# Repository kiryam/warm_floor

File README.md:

# Absolutely no warranty USE ON YOUR OWN RISK

# About this project
This project I started when I finished my home lab in balcony of my house.
I found that it is very cold in december. I decided to install floor heater to make temperature comfortable,
but first attempt been wrong. I had very hot floor. I decided to make floor heater with 5 zones (unformattly right now device have support for 6 zones)

# Hardware
## High voltage module
todo

## Logic module
todo

## Controller module
todo

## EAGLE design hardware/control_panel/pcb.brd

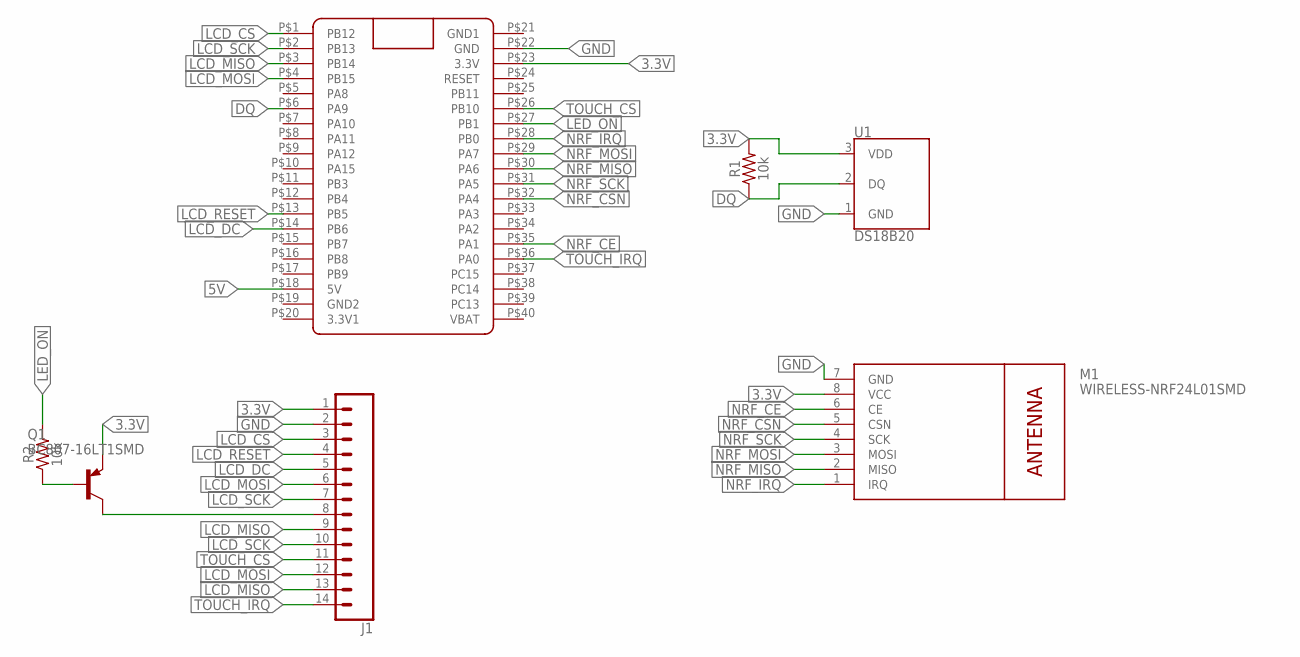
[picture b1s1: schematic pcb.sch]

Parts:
J1: CONN_14; 1X14
M1: WIRELESS-NRF24L01SMD; WIRELESS-NRF24L01-SMD
Q1: BC807-16LT1SMD; SOT23-BEC
R1, R2: 10k; 0603
U1: DS18B20; TO-92-AMMO
U$1: BLUE_PILL

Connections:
3.3V: J1.1, M1.8 (VCC), Q1.E, R1.2, U1.3 (VDD), U$1.P$23 (3.3V)
5V: U$1.P$18 (5V)
DQ: R1.1, U1.2 (DQ), U$1.P$6 (PA9)
GND: J1.2, M1.7 (GND), U1.1 (GND), U$1.P$22 (GND)
GND1: U$1.P$21 (GND1)
LCD_CS: J1.3, U$1.P$1 (PB12)
LCD_DC: J1.5, U$1.P$14 (PB6)
LCD_MISO: J1.9, J1.13, U$1.P$3 (PB14)
LCD_MOSI: J1.6, J1.12, U$1.P$4 (PB15)
LCD_RESET: J1.4, U$1.P$13 (PB5)
LCD_SCK: J1.7, J1.10, U$1.P$2 (PB13)
LED_ON: R2.2, U$1.P$27 (PB1)
unnamed: Q1.B, R2.1
unnamed: J1.8, Q1.C
NRF_CE: M1.6 (CE), U$1.P$35 (PA1)
NRF_CSN: M1.5 (CSN), U$1.P$32 (PA4)
NRF_IRQ: M1.1 (IRQ), U$1.P$28 (PB0)
NRF_MISO: M1.2 (MISO), U$1.P$30 (PA6)
NRF_MOSI: M1.3 (MOSI), U$1.P$29 (PA7)
NRF_SCK: M1.4 (SCK), U$1.P$31 (PA5)
TOUCH_CS: J1.11, U$1.P$26 (PB10)
TOUCH_IRQ: J1.14, U$1.P$36 (PA0)

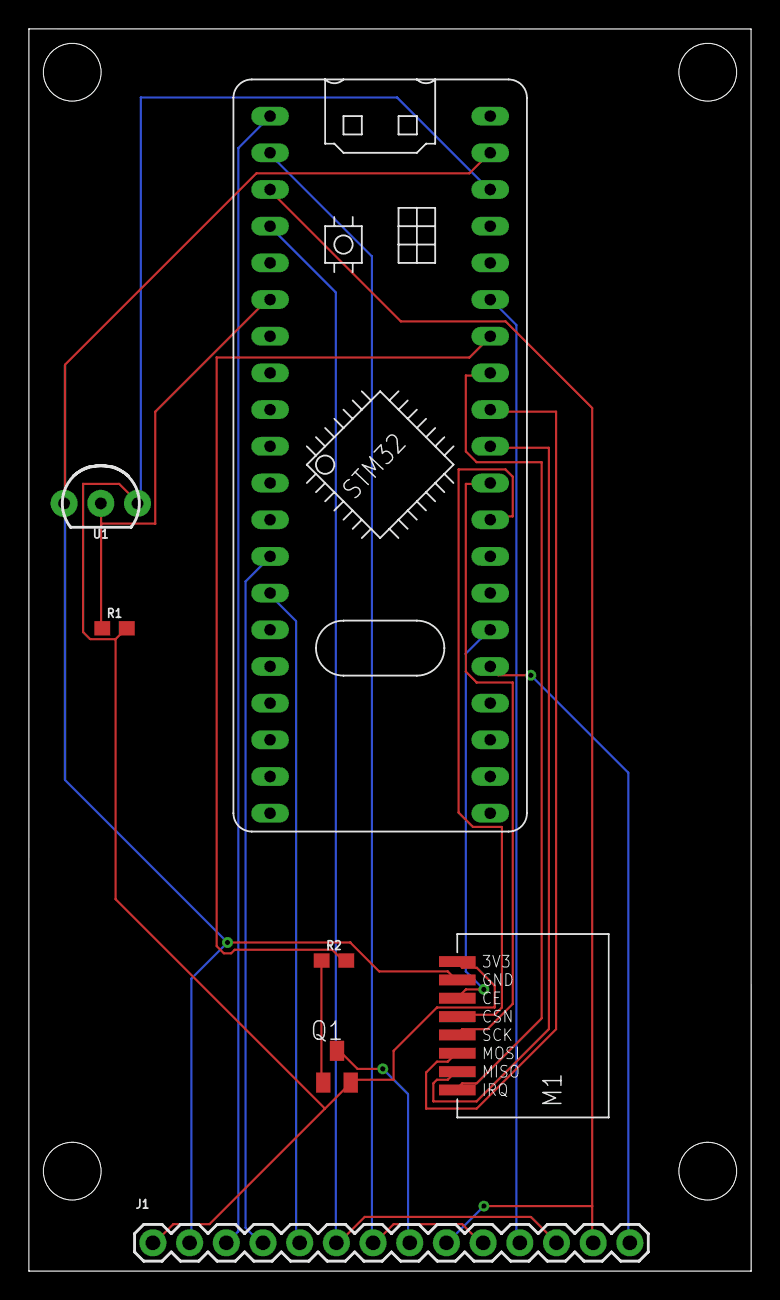
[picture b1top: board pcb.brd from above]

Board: 2 copper layers, 50.0 x 86.0 mm, 7 parts (0 on the bottom side), 20 nets.

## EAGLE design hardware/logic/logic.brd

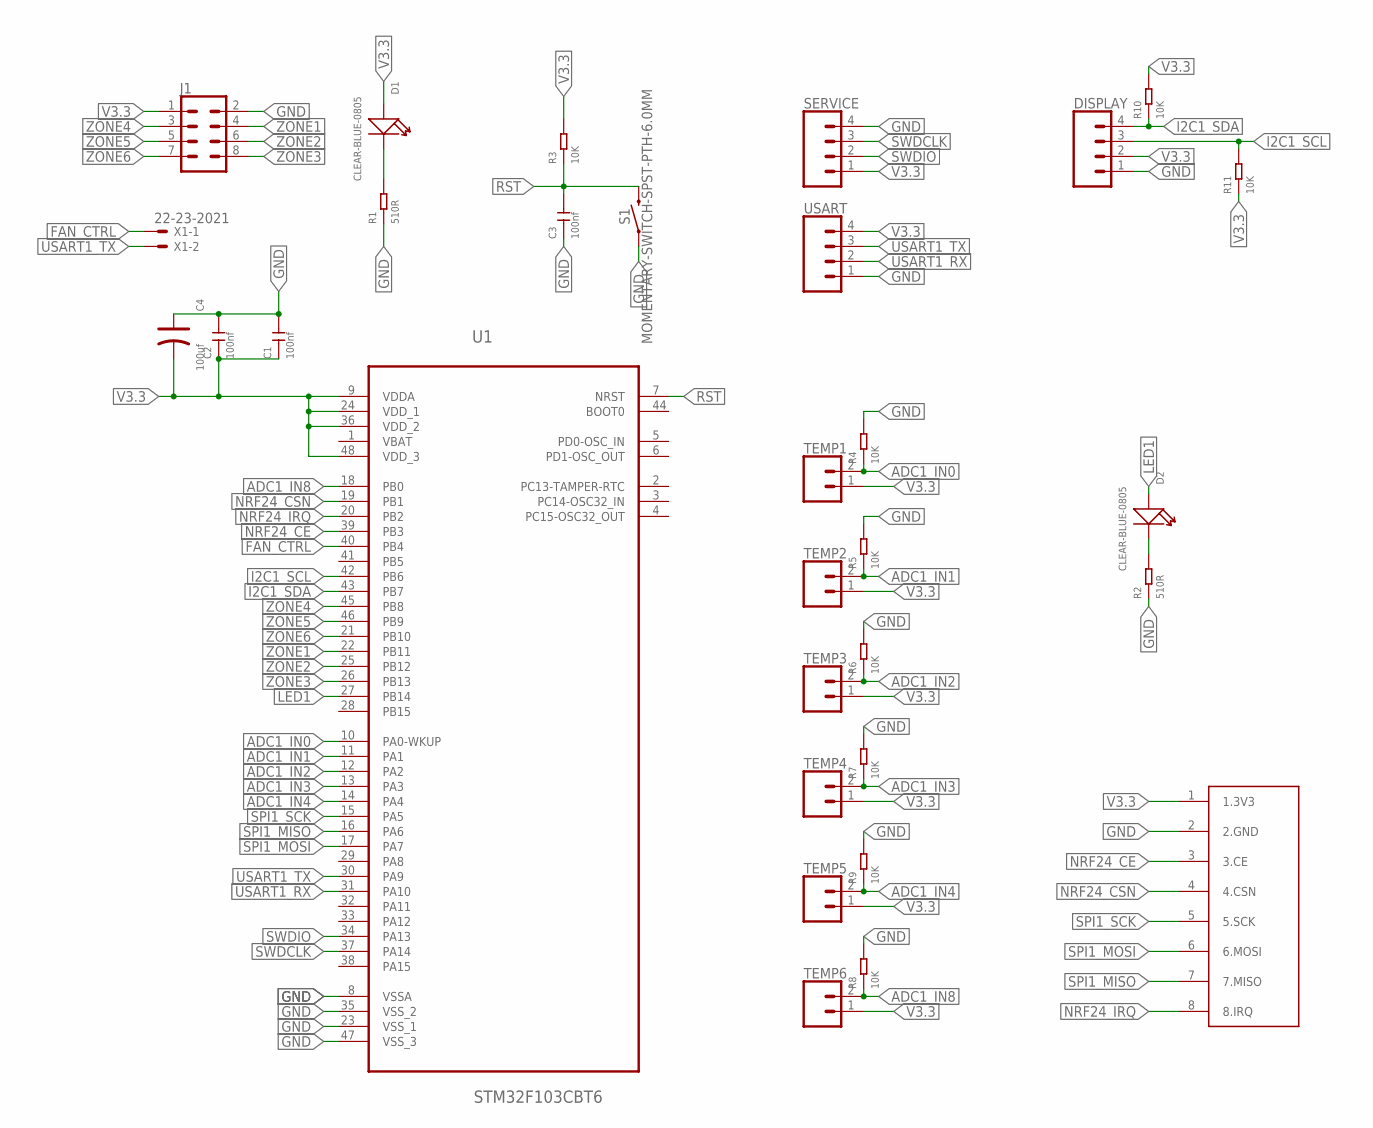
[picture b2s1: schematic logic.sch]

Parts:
C1, C2, C3: 100nf; C0805
C4: 100uf; AVX-B
D1, D2: CLEAR-BLUE-0805; LED-0805
DISPLAY: CONN_04; 1X04
J1: CONN_04X2; 2X4
R1, R2: 510R; R0603
R3, R4, R5, R6, R7, R8, R9, R10, R11: 10K; R0805
S1: MOMENTARY-SWITCH-SPST-PTH-6.0MM; TACTILE_SWITCH_PTH_6.0MM
SERVICE: CONN_04; 1X04
TEMP1, TEMP2, TEMP3, TEMP4, TEMP5, TEMP6: CONN_02; 1X02
U1: STM32F103CBT6; QFP50P900X900X160-48N
U$2: NRF24L01+
USART: CONN_04; 1X04
X1: 22-23-2021

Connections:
ADC1_IN0: R4.1, TEMP1.2, U1.10 (PA0-WKUP)
ADC1_IN1: R5.1, TEMP2.2, U1.11 (PA1)
ADC1_IN2: R6.1, TEMP3.2, U1.12 (PA2)
ADC1_IN3: R7.1, TEMP4.2, U1.13 (PA3)
ADC1_IN4: R9.1, TEMP5.2, U1.14 (PA4)
ADC1_IN8: R8.1, TEMP6.2, U1.18 (PB0)
FAN_CTRL: U1.40 (PB4), X1.1
GND: C1.2, C2.2, C3.1, C4.+, DISPLAY.1, J1.2, R1.1, R2.1, R4.2, R5.2, R6.2, R7.2, R8.2, R9.2, S1.1, SERVICE.4, U1.8 (VSSA), U1.23 (VSS_1), U1.35 (VSS_2), U1.47 (VSS_3), U$2.2 (2.GND), USART.1
I2C1_SCL: DISPLAY.3, R11.2, U1.42 (PB6)
I2C1_SDA: DISPLAY.4, R10.1, U1.43 (PB7)
LED1: D2.+, U1.27 (PB14)
unnamed: D1.-, R1.2
unnamed: D2.-, R2.2
NRF24_CE: U1.39 (PB3), U$2.3 (3.CE)
NRF24_CSN: U1.19 (PB1), U$2.4 (4.CSN)
NRF24_IRQ: U1.20 (PB2), U$2.8 (8.IRQ)
PA11: U1.32 (PA11)
RST: C3.2, R3.1, S1.3 (2), U1.7 (NRST)
SPI1_MISO: U1.16 (PA6), U$2.7 (7.MISO)
SPI1_MOSI: U1.17 (PA7), U$2.6 (6.MOSI)
SPI1_SCK: U1.15 (PA5), U$2.5 (5.SCK)
SWDCLK: SERVICE.3, U1.37 (PA14)
SWDIO: SERVICE.2, U1.34 (PA13)
USART1_RX: U1.31 (PA10), USART.2
USART1_TX: U1.30 (PA9), USART.3, X1.2
V3.3: C1.1, C2.1, C4.-, D1.+, DISPLAY.2, J1.1, R3.2, R10.2, R11.1, SERVICE.1, TEMP1.1, TEMP2.1, TEMP3.1, TEMP4.1, TEMP5.1, TEMP6.1, U1.9 (VDDA), U1.24 (VDD_1), U1.36 (VDD_2), U1.48 (VDD_3), U$2.1 (1.3V3), USART.4
ZONE1: J1.4, U1.22 (PB11)
ZONE2: J1.6, U1.25 (PB12)
ZONE3: J1.8, U1.26 (PB13)
ZONE4: J1.3, U1.45 (PB8)
ZONE5: J1.5, U1.46 (PB9)
ZONE6: J1.7, U1.21 (PB10)

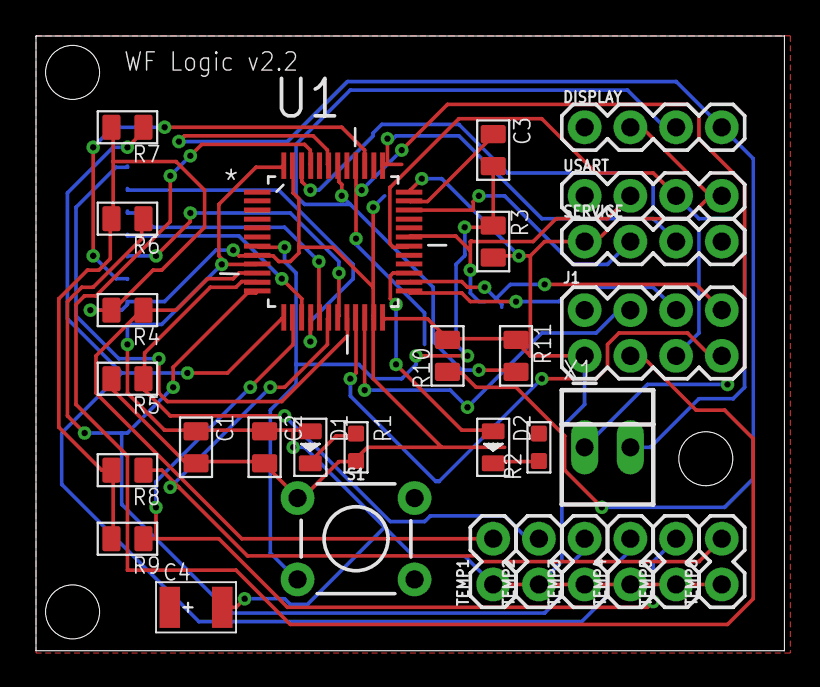
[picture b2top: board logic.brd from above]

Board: 2 copper layers, 41.6 x 34.2 mm, 31 parts (1 on the bottom side), 31 nets.

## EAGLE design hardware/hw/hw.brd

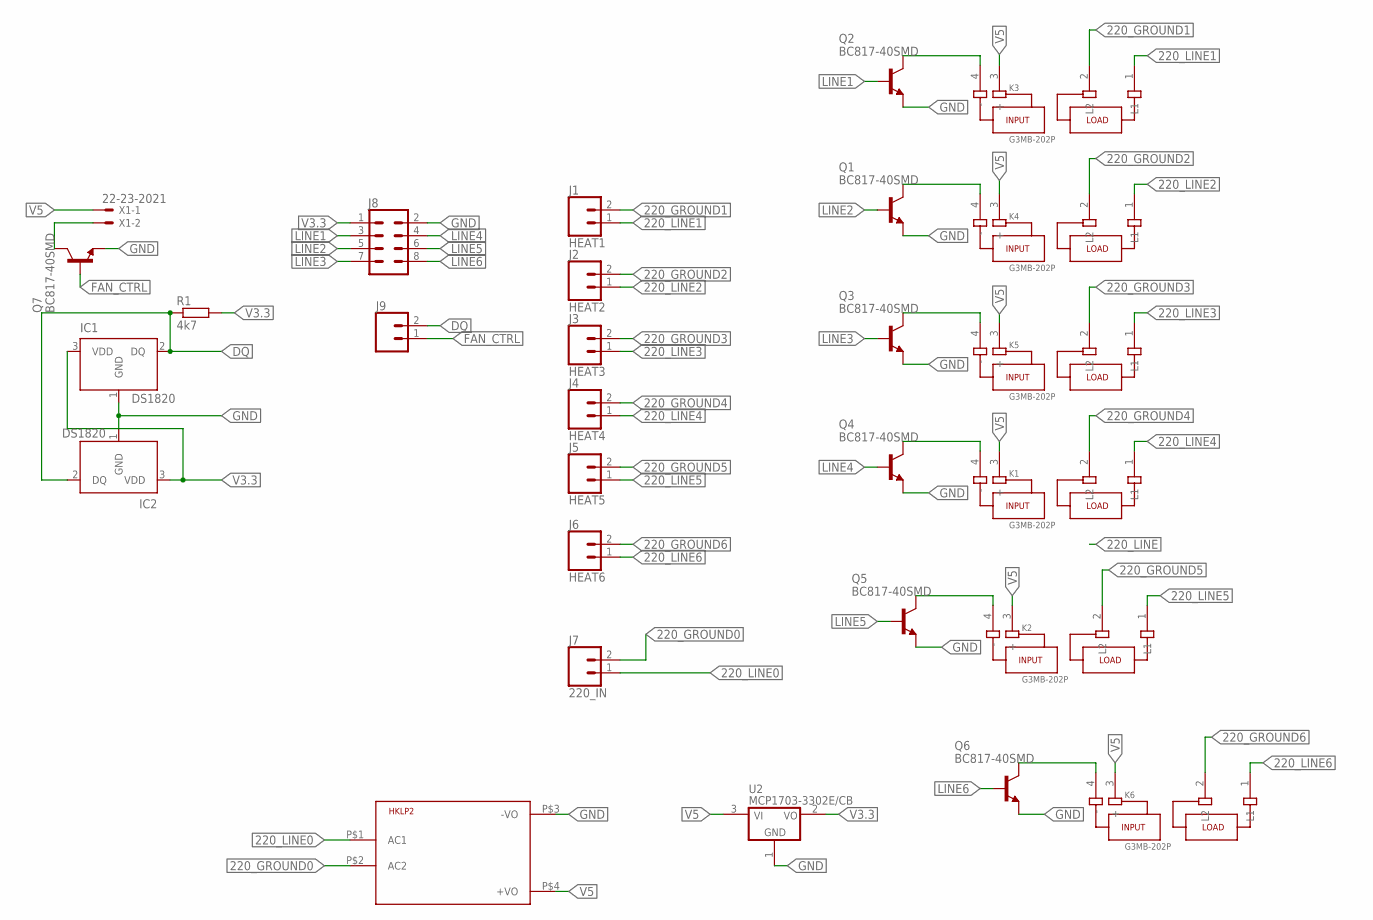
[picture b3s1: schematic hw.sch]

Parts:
HKLP2: HKLPM01
IC1, IC2: DS1820; TO-92
J1: HEAT1; SCREWTERMINAL-5MM-2
J2: HEAT2; SCREWTERMINAL-5MM-2
J3: HEAT3; SCREWTERMINAL-5MM-2
J4: HEAT4; SCREWTERMINAL-5MM-2
J5: HEAT5; SCREWTERMINAL-5MM-2
J6: HEAT6; SCREWTERMINAL-5MM-2
J7: 220_IN; SCREWTERMINAL-5MM-2
J8: CONN_04X2; 2X4
J9: CONN_02; 1X02
K1, K2, K3, K4, K5, K6: G3MB-202P; RELAY_G3MB-202P
Q1, Q2, Q3, Q4, Q5, Q6, Q7: BC817-40SMD; SOT23-BEC
R1: 4k7; R0805
U2: MCP1703-3302E/CB; SOT23A_MICROCHIP_CB
X1: 22-23-2021

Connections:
220_GROUND0: HKLP2.P$2 (AC2), J7.2
220_GROUND1: J1.2, K3.2 (L2)
220_GROUND2: J2.2, K4.2 (L2)
220_GROUND3: J3.2, K5.2 (L2)
220_GROUND4: J4.2, K1.2 (L2)
220_GROUND5: J5.2, K2.2 (L2)
220_GROUND6: J6.2, K6.2 (L2)
220_LINE0: HKLP2.P$1 (AC1), J7.1
220_LINE1: J1.1, K3.1 (L1)
220_LINE2: J2.1, K4.1 (L1)
220_LINE3: J3.1, K5.1 (L1)
220_LINE4: J4.1, K1.1 (L1)
220_LINE5: J5.1, K2.1 (L1)
220_LINE6: J6.1, K6.1 (L1)
DQ: IC1.2 (DQ), IC2.2 (DQ), J9.2, R1.1
FAN_CTRL: J9.1, Q7.B
GND: HKLP2.P$3 (-VO), IC1.1 (GND), IC2.1 (GND), J8.2, Q1.E, Q2.E, Q3.E, Q4.E, Q5.E, Q6.E, Q7.E, U2.1 (GND)
LINE1: J8.3, Q2.B
LINE2: J8.5, Q1.B
LINE3: J8.7, Q3.B
LINE4: J8.4, Q4.B
LINE5: J8.6, Q5.B
LINE6: J8.8, Q6.B
unnamed: K2.4 (-), Q5.C
unnamed: K3.4 (-), Q2.C
unnamed: K6.4 (-), Q6.C
unnamed: K4.4 (-), Q1.C
unnamed: K5.4 (-), Q3.C
unnamed: K1.4 (-), Q4.C
unnamed: Q7.C, X1.2
V3.3: IC1.3 (VDD), IC2.3 (VDD), J8.1, R1.2, U2.2 (VO)
V5: HKLP2.P$4 (+VO), K1.3 (+), K2.3 (+), K3.3 (+), K4.3 (+), K5.3 (+), K6.3 (+), U2.3 (VI), X1.1

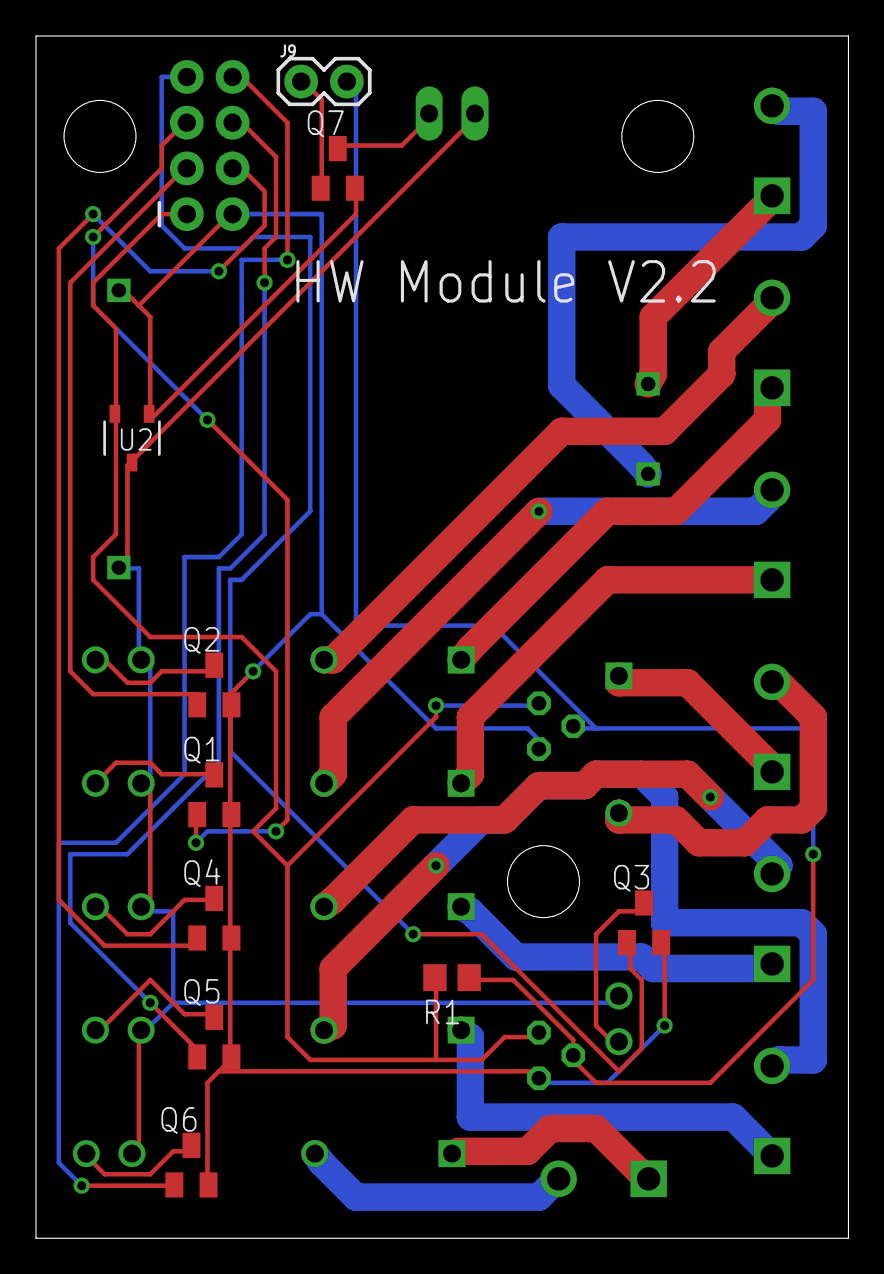
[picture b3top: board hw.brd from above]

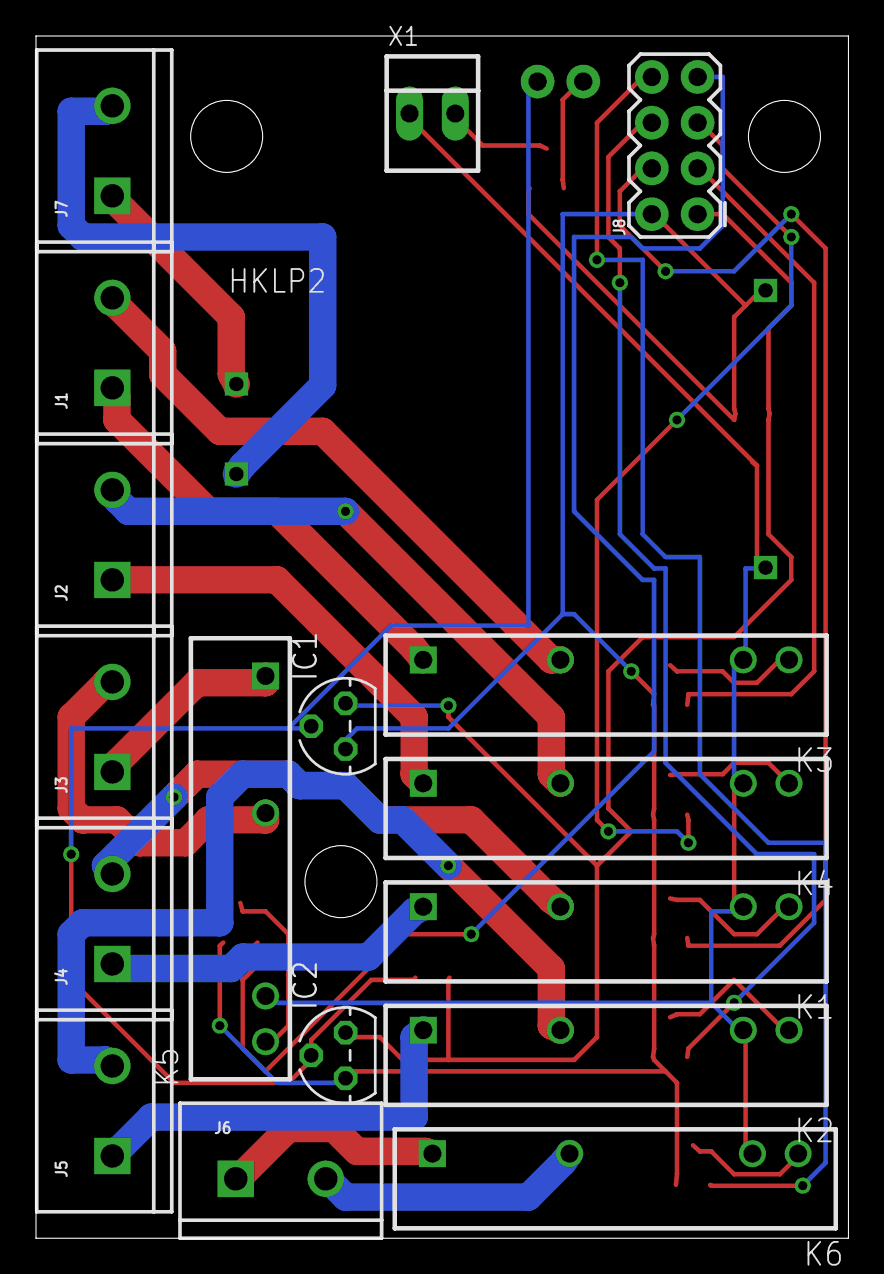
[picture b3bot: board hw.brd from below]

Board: 2 copper layers, 45.1 x 66.8 mm, 28 parts (18 on the bottom side), 32 nets.

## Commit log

2018-06-06 hardware
2018-06-06 firmware
2018-06-06 fusion sync
2018-06-10 small imporovements
2018-09-04 fixes in logic board. now support 6 channels. add debug
2018-10-21 logic version 2.2
2018-10-26 change MCP1703 to LM1117 800mah add change
2018-11-06 pww for fan. control_panel pcb
2019-03-10 soft pwm tuning for fan
2020-05-17 migrate from eclipse project to basic Makefile also add support vs code
2020-05-17 small code cleanup
2020-05-17 add safety feature turn off heaters if not commands in 10 minutes

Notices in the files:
parts and their libraries:
SparkFun-Connectors: Licensing: Creative Commons ShareAlike 4.0 International - https://creativecommons.org/licenses/by-sa/4.0
